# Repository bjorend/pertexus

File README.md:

# Pertexus

## Introduction
Pertexus is a board design and firmware to allow control of
Pertec-type tape interface devices.  The board is designed around
the Teensy 4.1 board (https://www.pjrc.com/store/teensy41.html)

## Hardware Design

## Firmware

The firmware is built and programmed with the Arduino 1.8.19 GUI with the
Teensyduino 1.56 add-in (https://www.pjrc.com/teensy/td_download.html).

## Usage

The firmware presents a USB "serial" device to which a user can connect.
It implements a simple command line interface.

## Regular Commands

### date - Get or set the current date and time

#### Usage

date [MMDDhhmm[[CC]YY][.ss]]

#### Examples

To set the date:

```
PERTEXUS> date 112921532022
Tue Nov 29 21:53:08 2022
```

Sets the date to November 29, 2022, 9:53PM.

### density

### echo

### fsf

### help

### nop

### read

### reset

### rewind

### sd - Commands relating to SD storage

#### Usage
```
sd init|dir|read|rm
```

The `sd` command can:
* initialize communication with an SD card.  Note: it does not "initialize"
the SD card as in "format" it; the SD card must be already formatted in FAT32
format.
* list the contents of the SD card
* perform a test read of a tape file from the SD card (to measure performance)
* remove a single file from the SD card

### stats

### unload

### write

### erase

## Development/Debugging Commands

### cmd

### dump

### gpio

### peek

### play

### poke

### tapetest

### testread

### testwrite

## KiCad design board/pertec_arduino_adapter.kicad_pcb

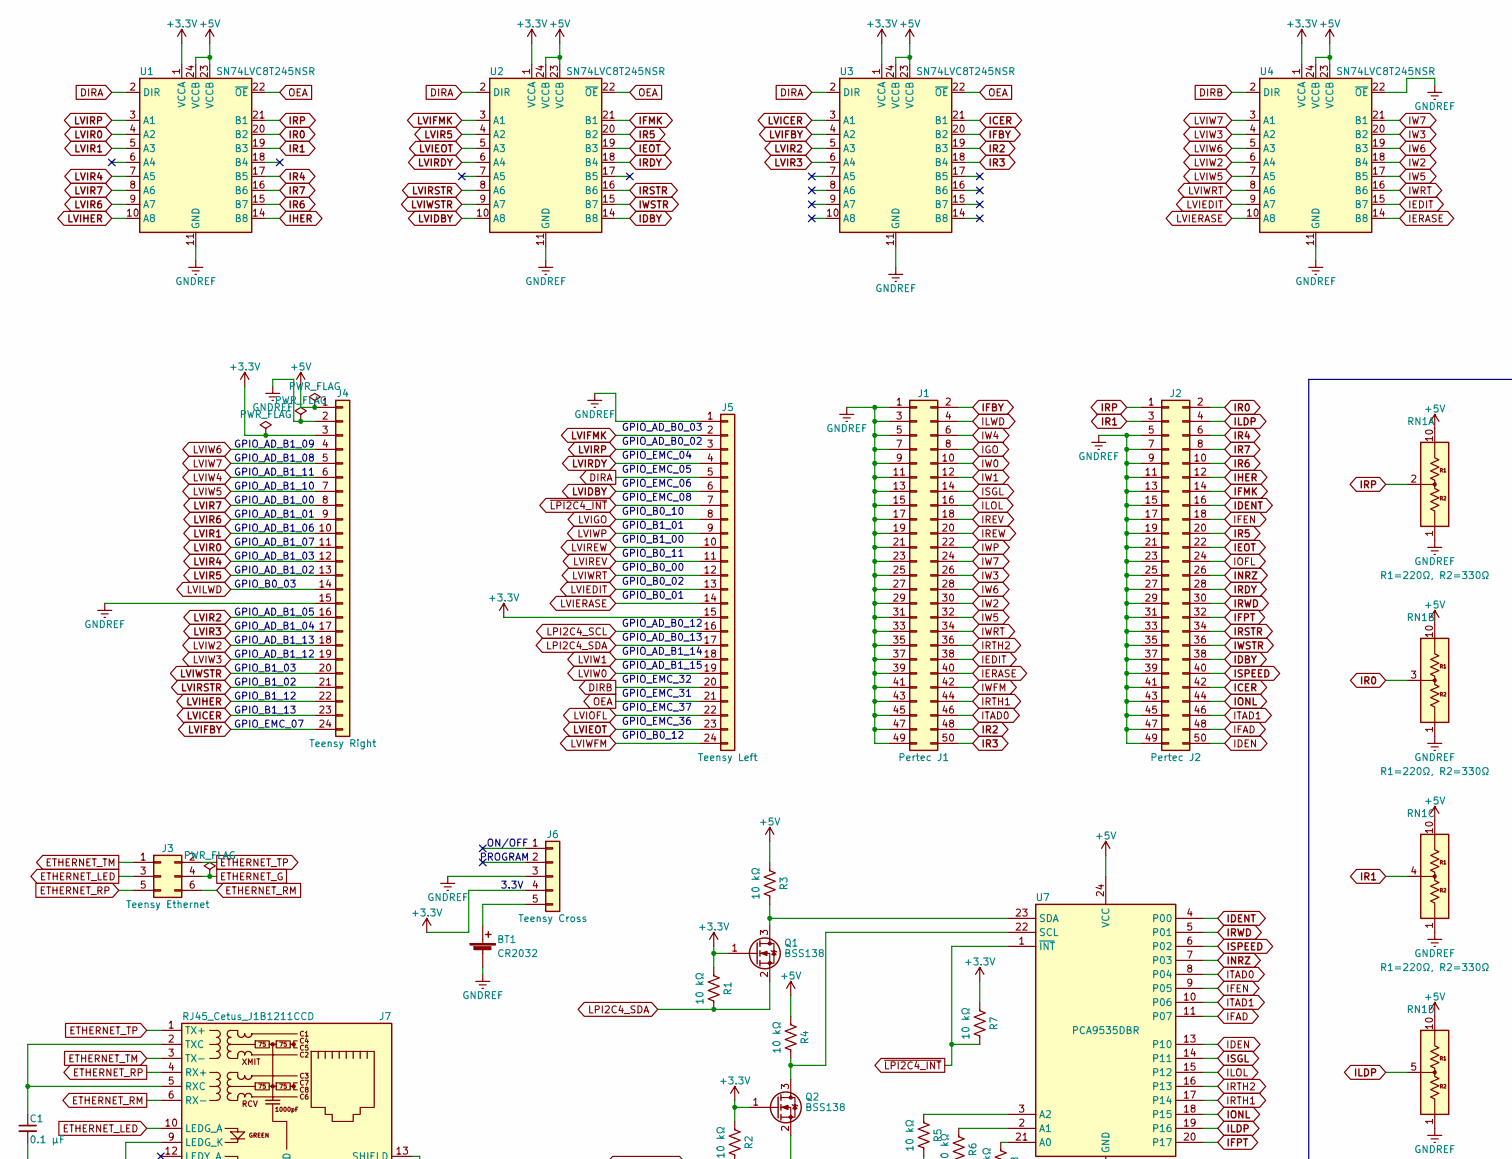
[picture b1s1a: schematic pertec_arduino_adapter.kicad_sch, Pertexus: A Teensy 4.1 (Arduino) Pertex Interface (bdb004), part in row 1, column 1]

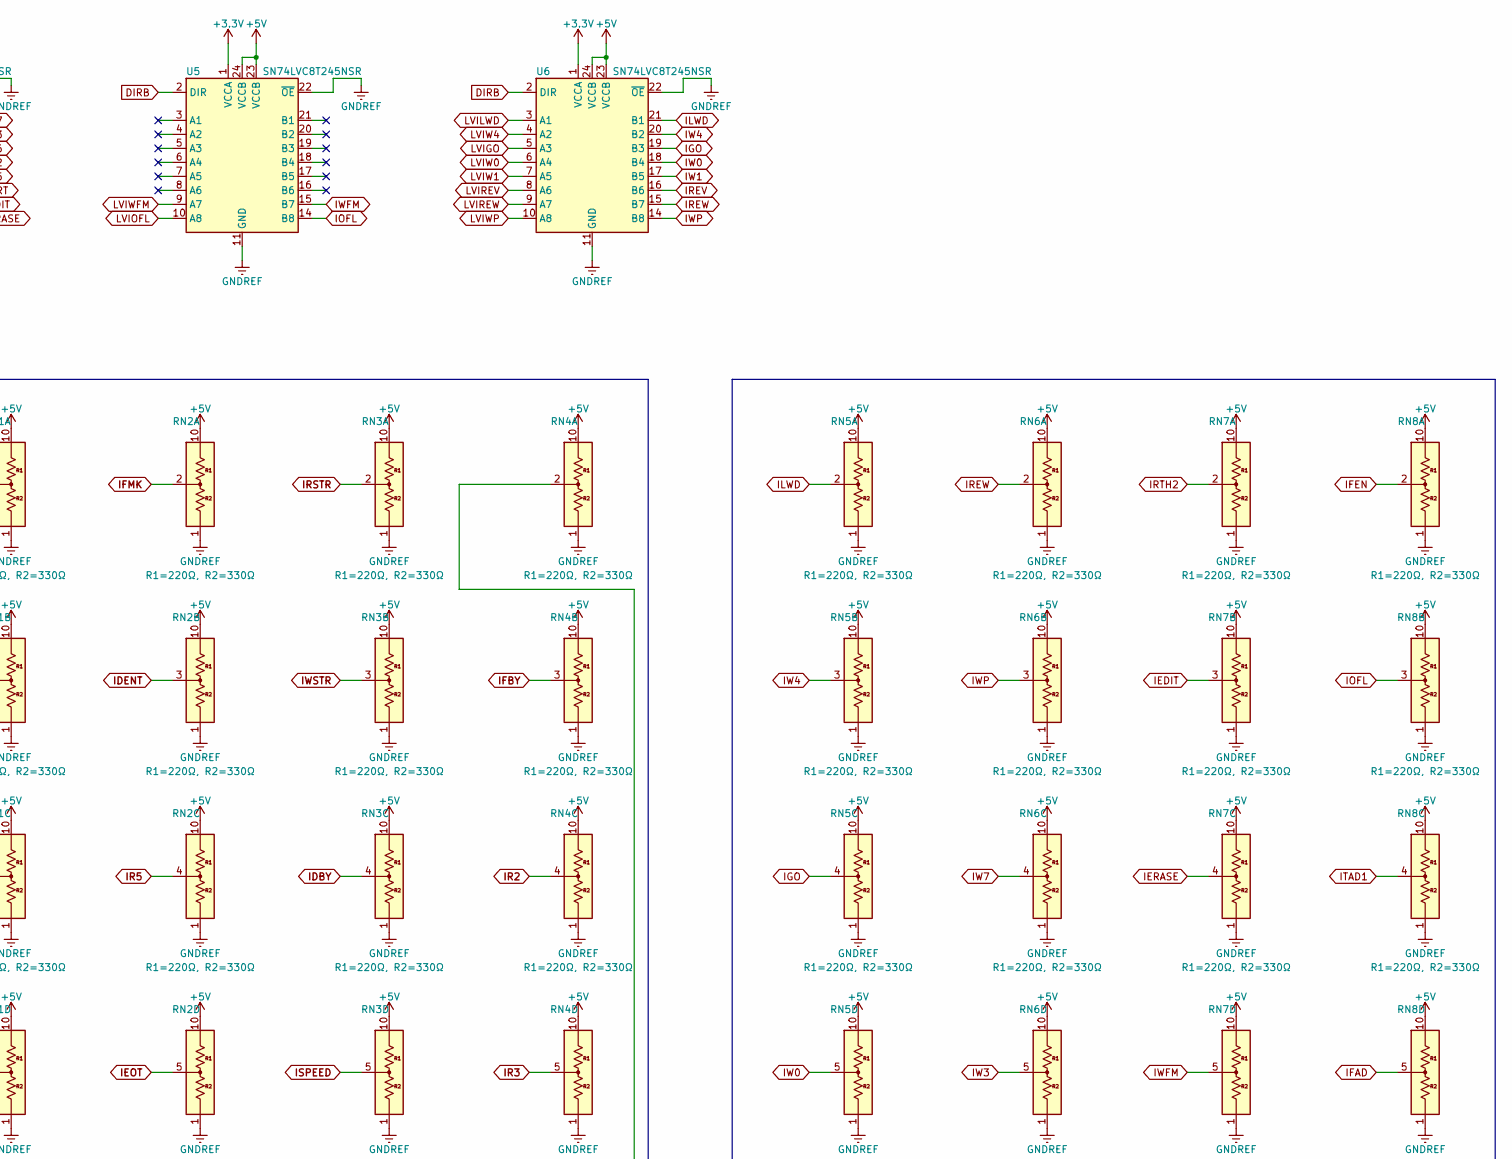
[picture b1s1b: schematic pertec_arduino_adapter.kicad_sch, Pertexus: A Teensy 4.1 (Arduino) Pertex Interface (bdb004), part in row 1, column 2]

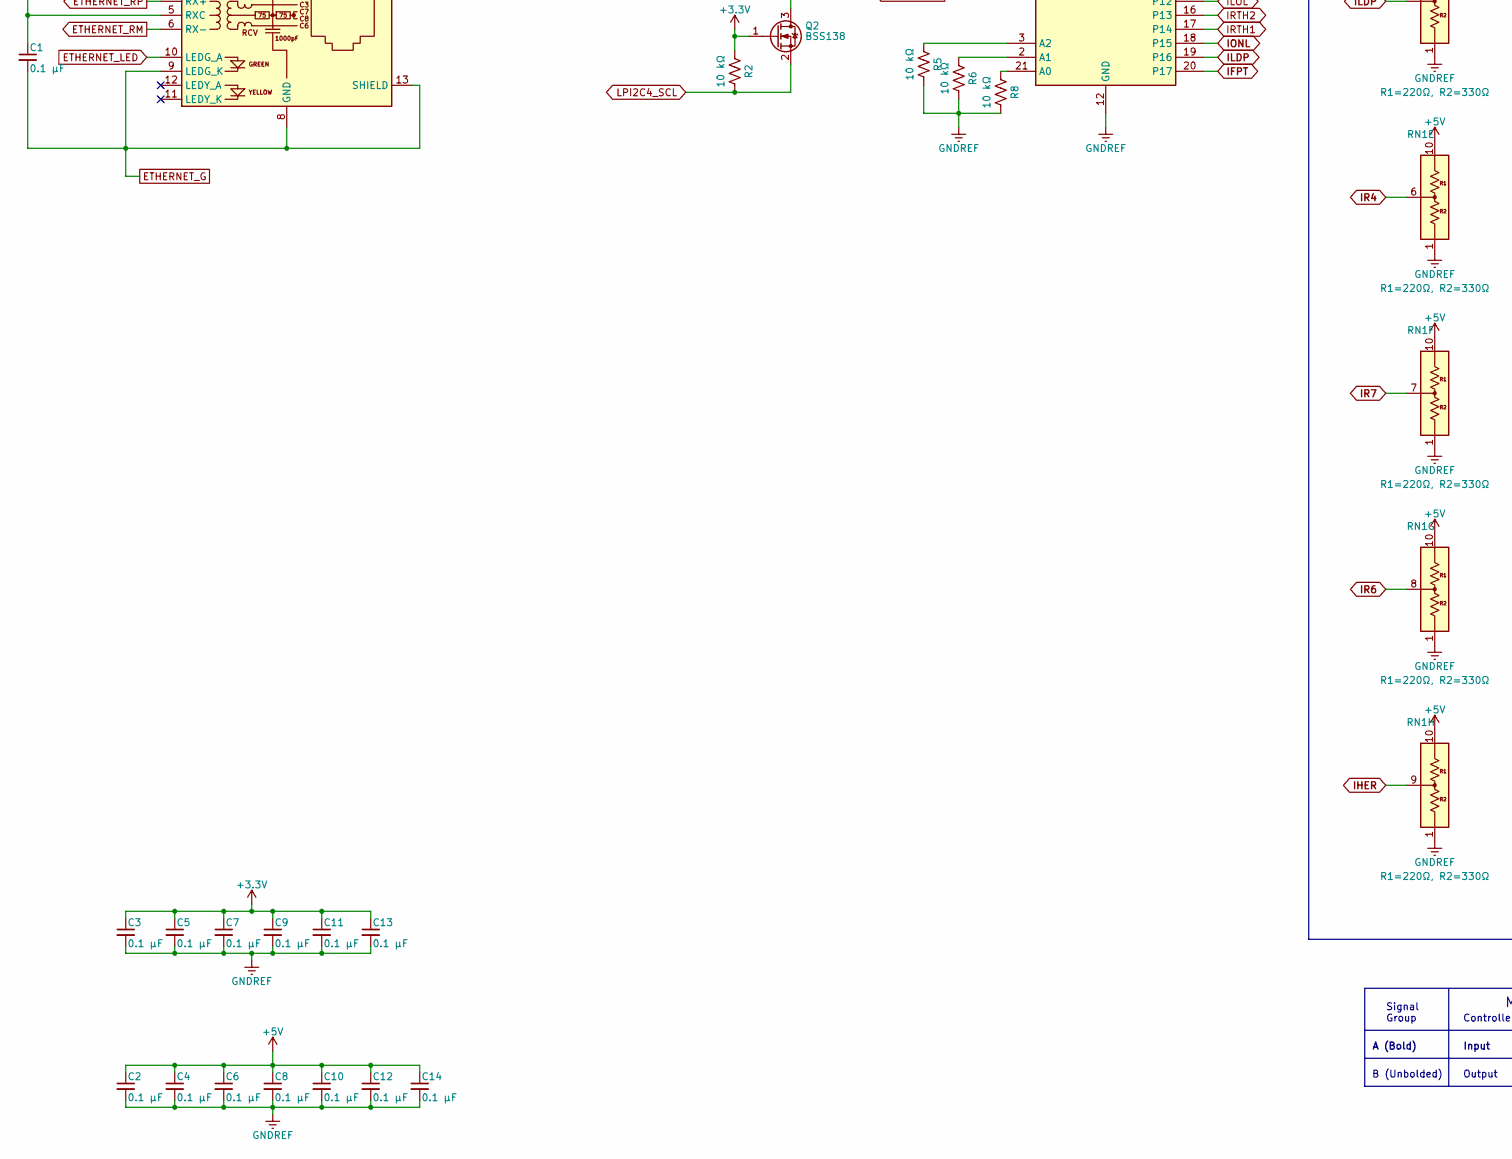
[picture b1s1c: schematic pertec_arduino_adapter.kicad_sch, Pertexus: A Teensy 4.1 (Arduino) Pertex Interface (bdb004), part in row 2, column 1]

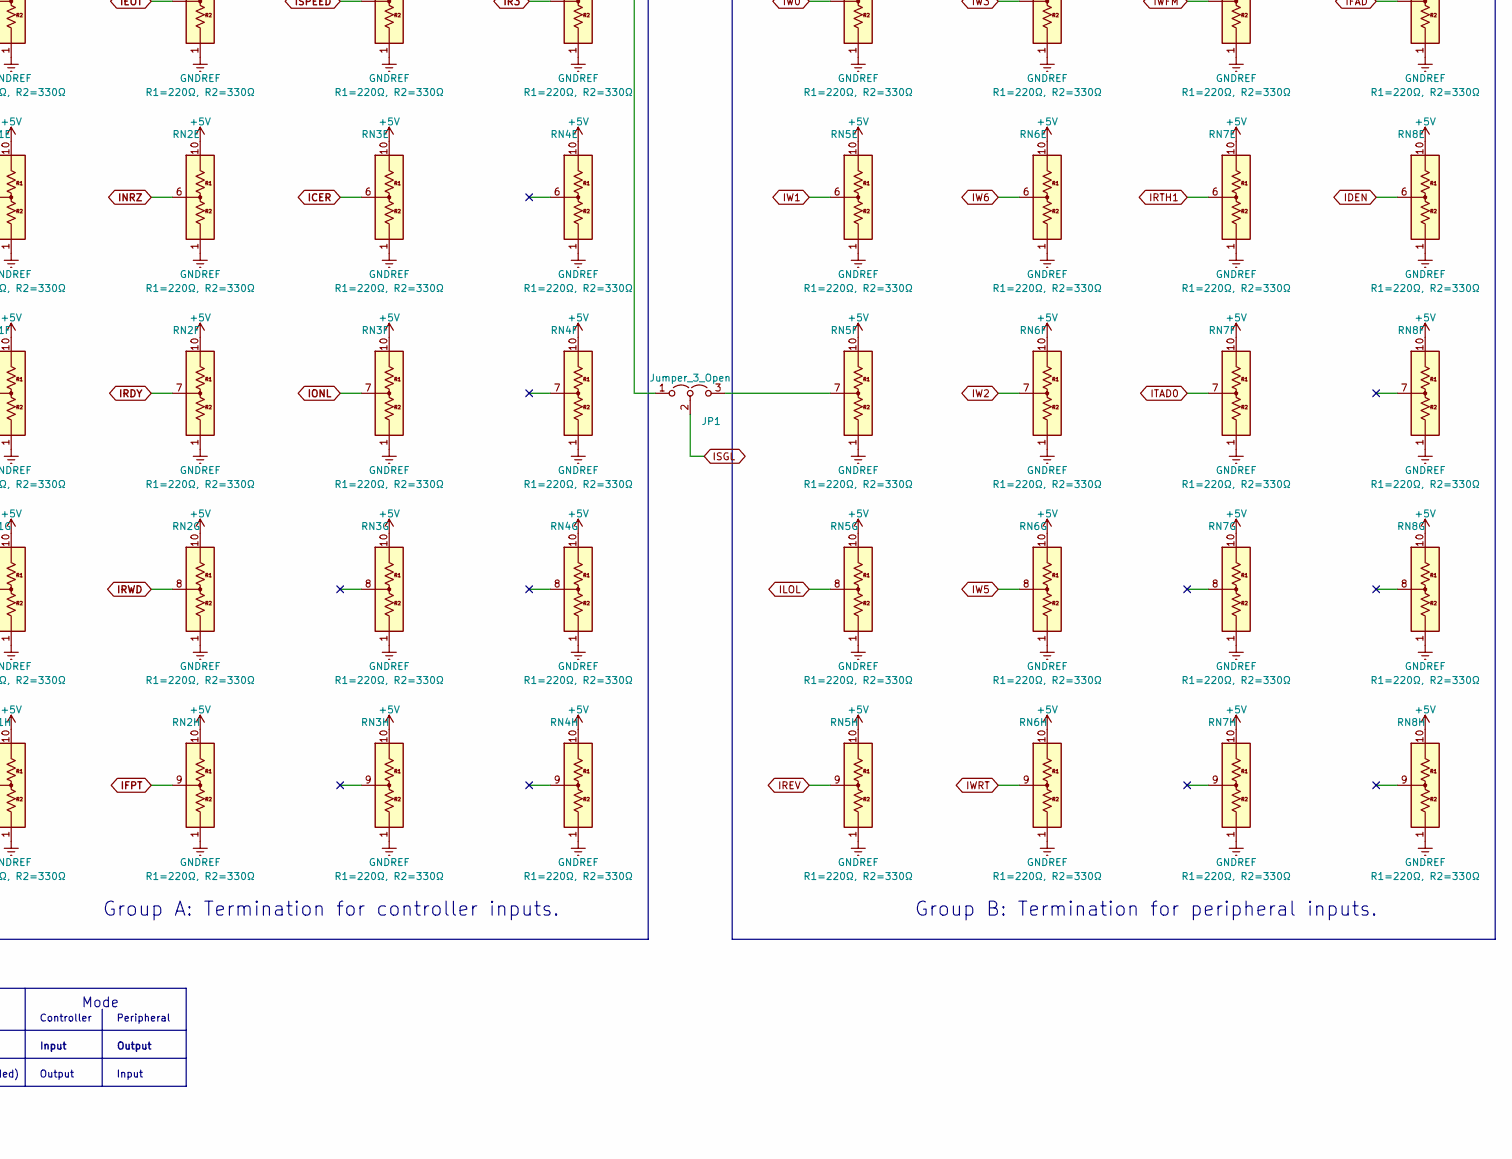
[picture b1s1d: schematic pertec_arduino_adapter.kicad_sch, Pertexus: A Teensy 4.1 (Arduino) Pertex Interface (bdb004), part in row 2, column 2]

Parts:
BT1: CR2032; BatteryHolder_Keystone_1058_1x2032
C1: 0.1 μF; C_Rect_L4.0mm_W2.5mm_P2.50mm
C2, C3, C4, C5, C6, C7, C8, C9, C10, C11, C12, C13, C14: 0.1 μF; C_0805_2012Metric_Pad1.18x1.45mm_HandSolder
J1: Pertec J1; IDC-Header_2x25_P2.54mm_Latch_Vertical
J2: Pertec J2; IDC-Header_2x25_P2.54mm_Latch_Vertical
J3: Teensy Ethernet; PinSocket_2x03_P2.00mm_Vertical_Mirror_Teensy4.1_J3
J4: Teensy Right; PinSocket_1x24_P2.54mm_Vertical_Teensy4.1_J4
J5: Teensy Left; PinSocket_1x24_P2.54mm_Vertical_Teensy4.1_J5
J6: Teensy Cross; PinSocket_1x05_P2.54mm_Vertical_Teensy4.1_J6
J7: RJ45_Cetus_J1B1211CCD; RJ45_Cetus_J1B1211CCD_Horizontal
JP1: Jumper_3_Open; PinHeader_1x03_P2.54mm_Vertical
Q1, Q2: BSS138; SOT-23
R1, R2, R3, R4, R5, R6, R7, R8: 10 kΩ; R_0805_2012Metric_Pad1.20x1.40mm_HandSolder
RN1, RN2, RN3, RN4, RN5, RN6, RN7, RN8: R1=220Ω, R2=330Ω; R_Array_SIP10
U1, U2, U3, U4, U5, U6: SN74LVC8T245NSR; SO-24_5.3x15mm_P1.27mm
U7: PCA9535DBR; SOIC-24W_7.5x15.4mm_P1.27mm

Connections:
+3V3: C3.1, C5.1, C7.1, C9.1, C11.1, C13.1, J4.3, J5.15, J6.4, Q1.1 (G), Q2.1 (G), R1.1, R2.1, R7.1, U1.1 (VCCA), U2.1 (VCCA), U3.1 (VCCA), U4.1 (VCCA), U5.1 (VCCA), U6.1 (VCCA)
+5V: C2.1, C4.1, C6.1, C8.1, C10.1, C12.1, C14.1, J4.1, R3.1, R4.1, RN1.10, RN2.10, RN3.10, RN4.10, RN5.10, RN6.10, RN7.10, RN8.10, U1.23 (VCCB), U1.24 (VCCB), U2.23 (VCCB), U2.24 (VCCB), U3.23 (VCCB), U3.24 (VCCB), U4.23 (VCCB), U4.24 (VCCB), U5.23 (VCCB), U5.24 (VCCB), U6.23 (VCCB), U6.24 (VCCB), U7.24 (VCC)
DIRA: J5.5, U1.2 (DIR), U2.2 (DIR), U3.2 (DIR)
DIRB: J5.20, U4.2 (DIR), U5.2 (DIR), U6.2 (DIR)
ETHERNET_G: C1.2, J3.4, J7.8 (GND), J7.9 (LEDG_K), J7.13 (SHIELD)
ETHERNET_LED: J3.3, J7.10 (LEDG_A)
ETHERNET_RM: J3.6, J7.6 (RX-)
ETHERNET_RP: J3.5, J7.4 (RX+)
ETHERNET_TM: J3.1, J7.3 (TX-)
ETHERNET_TP: J3.2, J7.1 (TX+)
GNDREF: BT1.2 (-), C2.2, C3.2, C4.2, C5.2, C6.2, C7.2, C8.2, C9.2, C10.2, C11.2, C12.2, C13.2, C14.2, J1.1, J1.3, J1.5, J1.7, J1.9, J1.11, J1.13, J1.15, J1.17, J1.19, J1.21, J1.23, J1.25, J1.27, J1.29, J1.31, J1.33, J1.35, J1.37, J1.39, J1.41, J1.43, J1.45, J1.47, J1.49, J2.5, J2.7, J2.9, J2.11, J2.13, J2.15, J2.17, J2.19, J2.21, J2.23, J2.25, J2.27, J2.29, J2.31, J2.33, J2.35, J2.37, J2.39, J2.41, J2.43, J2.45, J2.47, J2.49, J4.2, J4.15, J5.1, J6.3, R5.2, R6.2, R8.2, RN1.1, RN2.1, RN3.1, RN4.1, RN5.1, RN6.1, RN7.1, RN8.1, U1.11 (GND), U1.12 (GND), U1.13 (GND), U2.11 (GND), U2.12 (GND), U2.13 (GND), U3.11 (GND), U3.12 (GND), U3.13 (GND), U4.11 (GND), U4.12 (GND), U4.13 (GND), U4.22 (~OE), U5.11 (GND), U5.12 (GND), U5.13 (GND), U5.22 (~OE), U6.11 (GND), U6.12 (GND), U6.13 (GND), U6.22 (~OE), U7.12 (GND)
ICER: J2.42, RN3.6, U3.21 (B1)
IDBY: J2.38, RN3.4, U2.14 (B8)
IDEN: J2.50, RN8.6, U7.13 (P10)
IDENT: J2.16, RN2.3, U7.4 (P00)
IEDIT: J1.38, RN7.3, U4.15 (B7)
IEOT: J2.22, RN2.5, U2.19 (B3)
IERASE: J1.40, RN7.4, U4.14 (B8)
IFAD: J2.48, RN8.5, U7.11 (P07)
IFBY: J1.2, RN4.3, U3.20 (B2)
IFEN: J2.18, RN8.2, U7.9 (P05)
IFMK: J2.14, RN2.2, U2.21 (B1)
IFPT: J2.32, RN2.9, U7.20 (P17)
IGO: J1.8, RN5.4, U6.19 (B3)
IHER: J2.12, RN1.9, U1.14 (B8)
ILDP: J2.4, RN1.5, U7.19 (P16)
ILOL: J1.16, RN5.8, U7.15 (P12)
ILWD: J1.4, RN5.2, U6.21 (B1)
INRZ: J2.26, RN2.6, U7.7 (P03)
IOFL: J2.24, RN8.3, U5.14 (B8)
IONL: J2.44, RN3.7, U7.18 (P15)
IR0: J2.2, RN1.3, U1.20 (B2)
IR1: J2.3, RN1.4, U1.19 (B3)
IR2: J1.48, RN4.4, U3.19 (B3)
IR3: J1.50, RN4.5, U3.18 (B4)
IR4: J2.6, RN1.6, U1.17 (B5)
IR5: J2.20, RN2.4, U2.20 (B2)
IR6: J2.10, RN1.8, U1.15 (B7)
IR7: J2.8, RN1.7, U1.16 (B6)
IRDY: J2.28, RN2.7, U2.18 (B4)
IREV: J1.18, RN5.9, U6.16 (B6)
IREW: J1.20, RN6.2, U6.15 (B7)
IRP: J2.1, RN1.2, U1.21 (B1)
IRSTR: J2.34, RN3.2, U2.16 (B6)
IRTH1: J1.44, RN7.6, U7.17 (P14)
IRTH2: J1.36, RN7.2, U7.16 (P13)
IRWD: J2.30, RN2.8, U7.5 (P01)
ISGL: J1.14, JP1.2 (C), U7.14 (P11)
ISPEED: J2.40, RN3.5, U7.6 (P02)
ITAD0: J1.46, RN7.7, U7.8 (P04)
ITAD1: J2.46, RN8.4, U7.10 (P06)
IW0: J1.10, RN5.5, U6.18 (B4)
IW1: J1.12, RN5.6, U6.17 (B5)
IW2: J1.30, RN6.7, U4.18 (B4)
IW3: J1.26, RN6.5, U4.20 (B2)
IW4: J1.6, RN5.3, U6.20 (B2)
IW5: J1.32, RN6.8, U4.17 (B5)
IW6: J1.28, RN6.6, U4.19 (B3)
IW7: J1.24, RN6.4, U4.21 (B1)
IWFM: J1.42, RN7.5, U5.15 (B7)
IWP: J1.22, RN6.3, U6.14 (B8)
IWRT: J1.34, RN6.9, U4.16 (B6)
IWSTR: J2.36, RN3.3, U2.15 (B7)
LPI2C4_SCL: J5.16, Q2.2 (S), R2.2
LPI2C4_SDA: J5.17, Q1.2 (S), R1.2
LVICER: J4.23, U3.3 (A1)
LVIDBY: J5.6, U2.10 (A8)
LVIEDIT: J5.13, U4.9 (A7)
LVIEOT: J5.23, U2.5 (A3)
LVIERASE: J5.14, U4.10 (A8)
LVIFBY: J4.24, U3.4 (A2)
LVIFMK: J5.2, U2.3 (A1)
LVIGO: J5.8, U6.5 (A3)
LVIHER: J4.22, U1.10 (A8)
LVILWD: J4.14, U6.3 (A1)
LVIOFL: J5.22, U5.10 (A8)
LVIR0: J4.11, U1.4 (A2)
LVIR1: J4.10, U1.5 (A3)
LVIR2: J4.16, U3.5 (A3)
LVIR3: J4.17, U3.6 (A4)
LVIR4: J4.12, U1.7 (A5)
LVIR5: J4.13, U2.4 (A2)
LVIR6: J4.9, U1.9 (A7)
LVIR7: J4.8, U1.8 (A6)
LVIRDY: J5.4, U2.6 (A4)
LVIREV: J5.11, U6.8 (A6)
LVIREW: J5.10, U6.9 (A7)
LVIRP: J5.3, U1.3 (A1)
LVIRSTR: J4.21, U2.8 (A6)
LVIW0: J5.19, U6.6 (A4)
LVIW1: J5.18, U6.7 (A5)
LVIW2: J4.18, U4.6 (A4)
LVIW3: J4.19, U4.4 (A2)
LVIW4: J4.6, U6.4 (A2)
LVIW5: J4.7, U4.7 (A5)
LVIW6: J4.4, U4.5 (A3)
LVIW7: J4.5, U4.3 (A1)
LVIWFM: J5.24, U5.9 (A7)
LVIWP: J5.9, U6.10 (A8)
LVIWRT: J5.12, U4.8 (A6)
LVIWSTR: J4.20, U2.9 (A7)
unnamed: BT1.1 (+), J6.5
unnamed: C1.1, J7.2 (TXC), J7.5 (RXC)
unnamed: JP1.1 (A), RN4.2
unnamed: JP1.3 (B), RN5.7
unnamed: Q1.3 (D), R3.2, U7.23 (SDA)
unnamed: Q2.3 (D), R4.2, U7.22 (SCL)
unnamed: R5.1, U7.3 (A2)
unnamed: R6.1, U7.2 (A1)
unnamed: R8.1, U7.21 (A0)
OEA: J5.21, U1.22 (~OE), U2.22 (~OE), U3.22 (~OE)
~LPI2C4_INT: J5.7, R7.2, U7.1 (~INT)

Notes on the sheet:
A (Bold)
GPIO_EMC_32
Controller
GPIO_B1_00
3.3V
GPIO_AD_B0_02
GPIO_B0_02
GPIO_AD_B1_13
GPIO_AD_B1_07
GPIO_AD_B0_13
GPIO_EMC_07
Input
GPIO_B1_12
Signal Group
GPIO_B0_11
Mode
GPIO_EMC_04
GPIO_AD_B1_10
Output
GPIO_AD_B1_03
PROGRAM
GPIO_AD_B0_12
Group B: Termination for peripheral inputs.
GPIO_B0_01
GPIO_B0_12
ON/OFF
Peripheral
GPIO_B0_00
GPIO_B1_03
GPIO_EMC_36
GPIO_AD_B1_15
GPIO_AD_B1_02
B (Unbolded)
GPIO_AD_B1_01
Group A: Termination for controller inputs.
GPIO_EMC_05
GPIO_EMC_06
GPIO_EMC_37
GPIO_AD_B0_03
GPIO_AD_B1_06

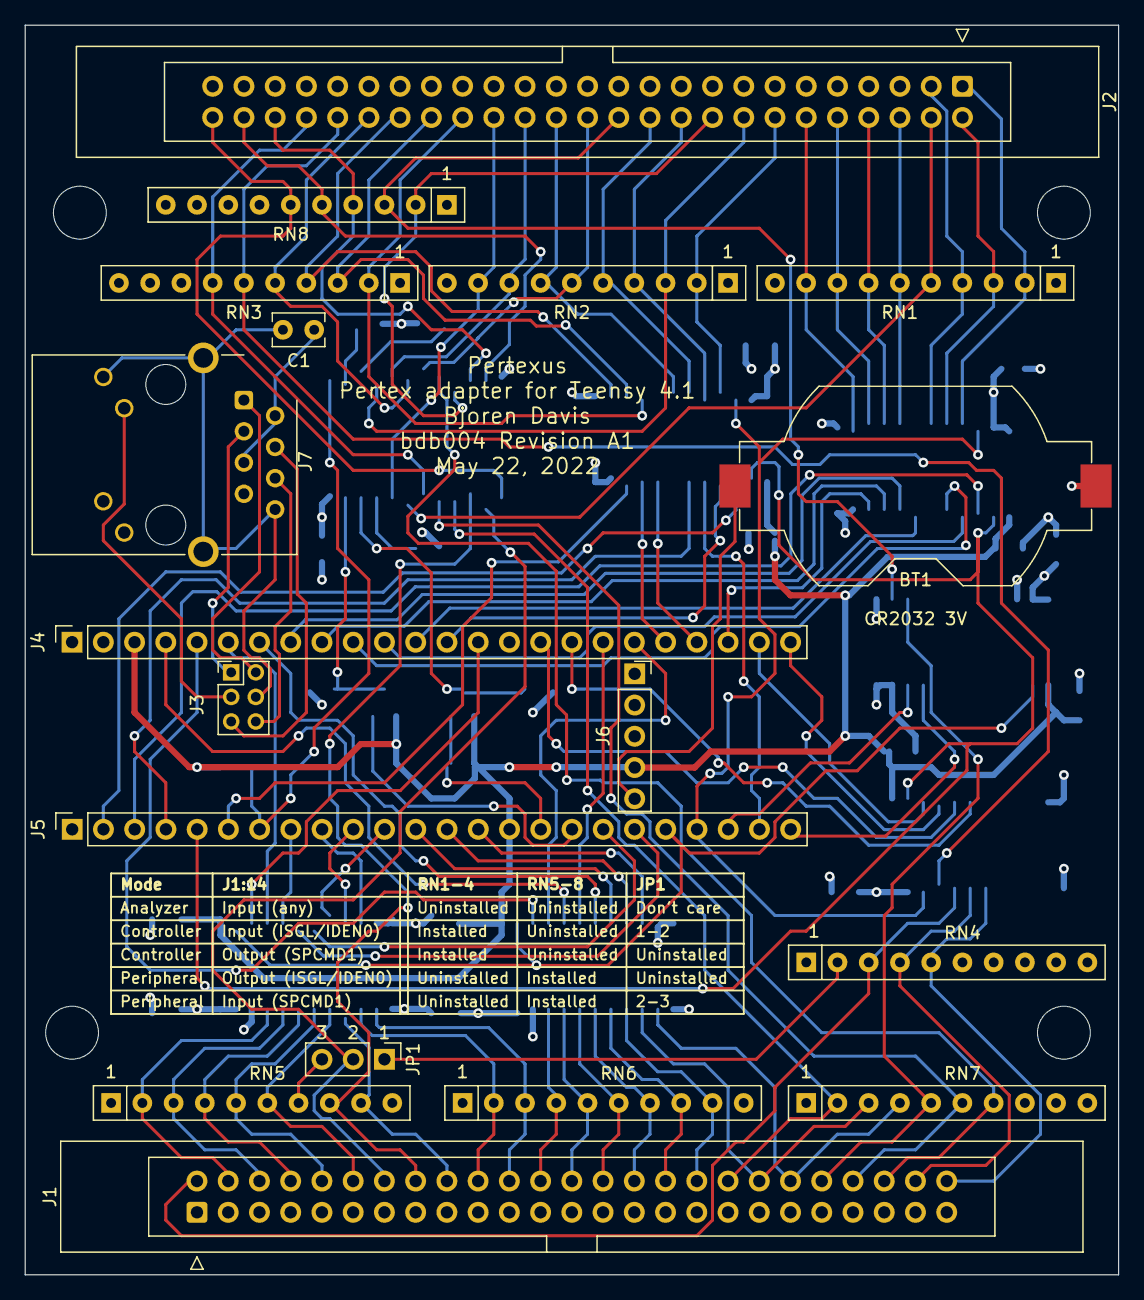
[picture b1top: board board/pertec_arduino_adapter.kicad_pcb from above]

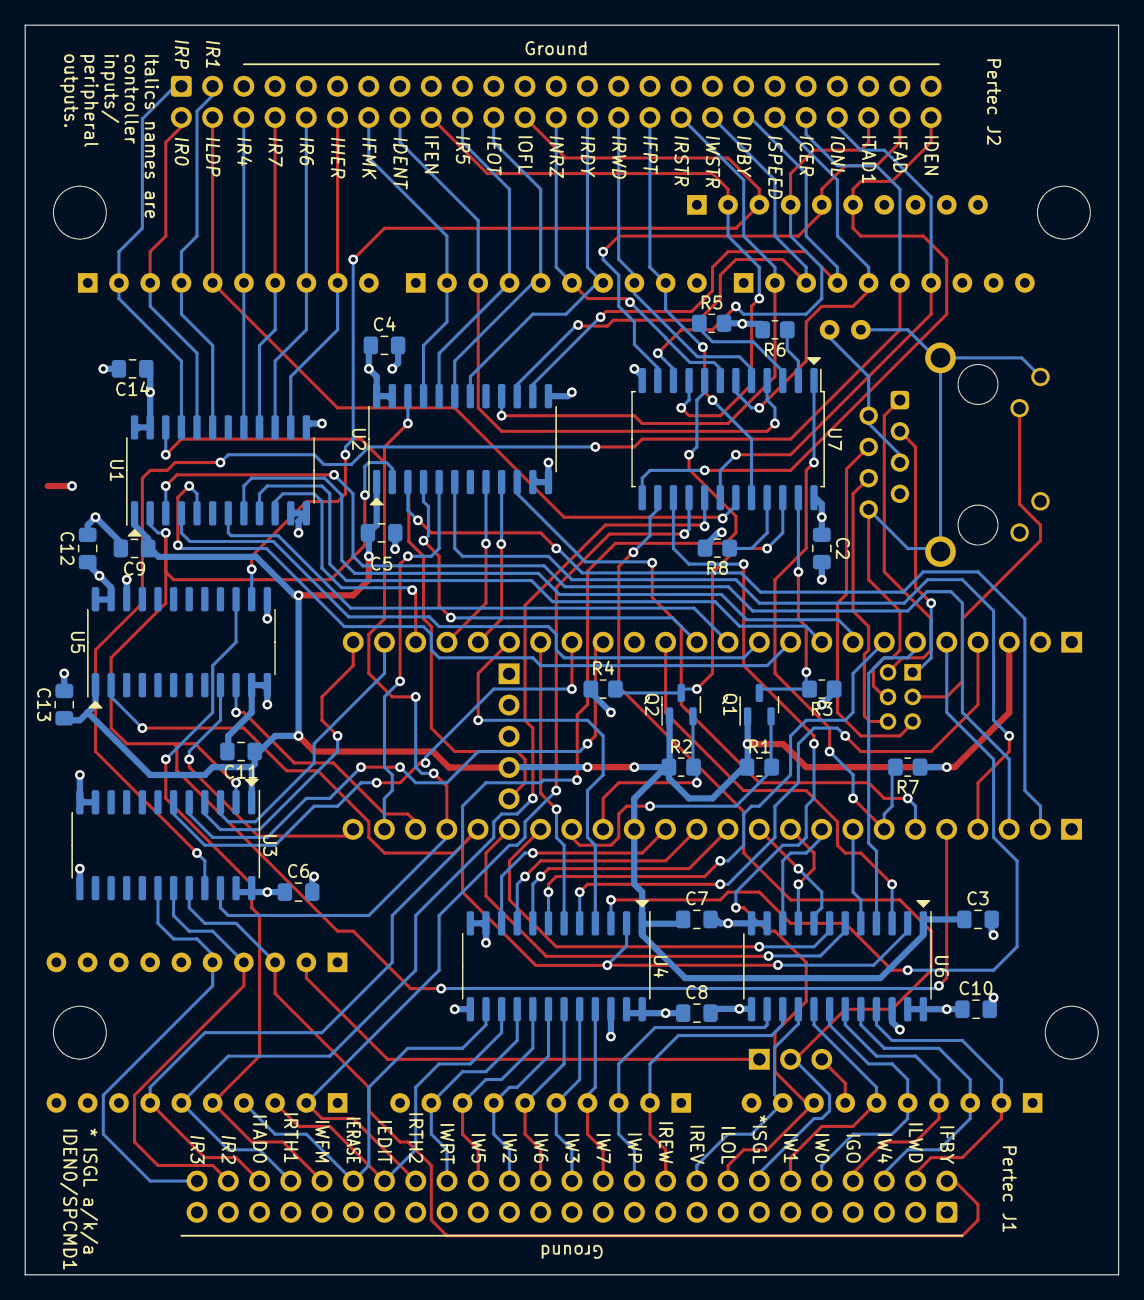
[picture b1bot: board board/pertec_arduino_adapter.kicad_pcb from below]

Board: 4 copper layers, 88.9 x 101.6 mm, 48 parts (30 on the bottom side), 112 nets.

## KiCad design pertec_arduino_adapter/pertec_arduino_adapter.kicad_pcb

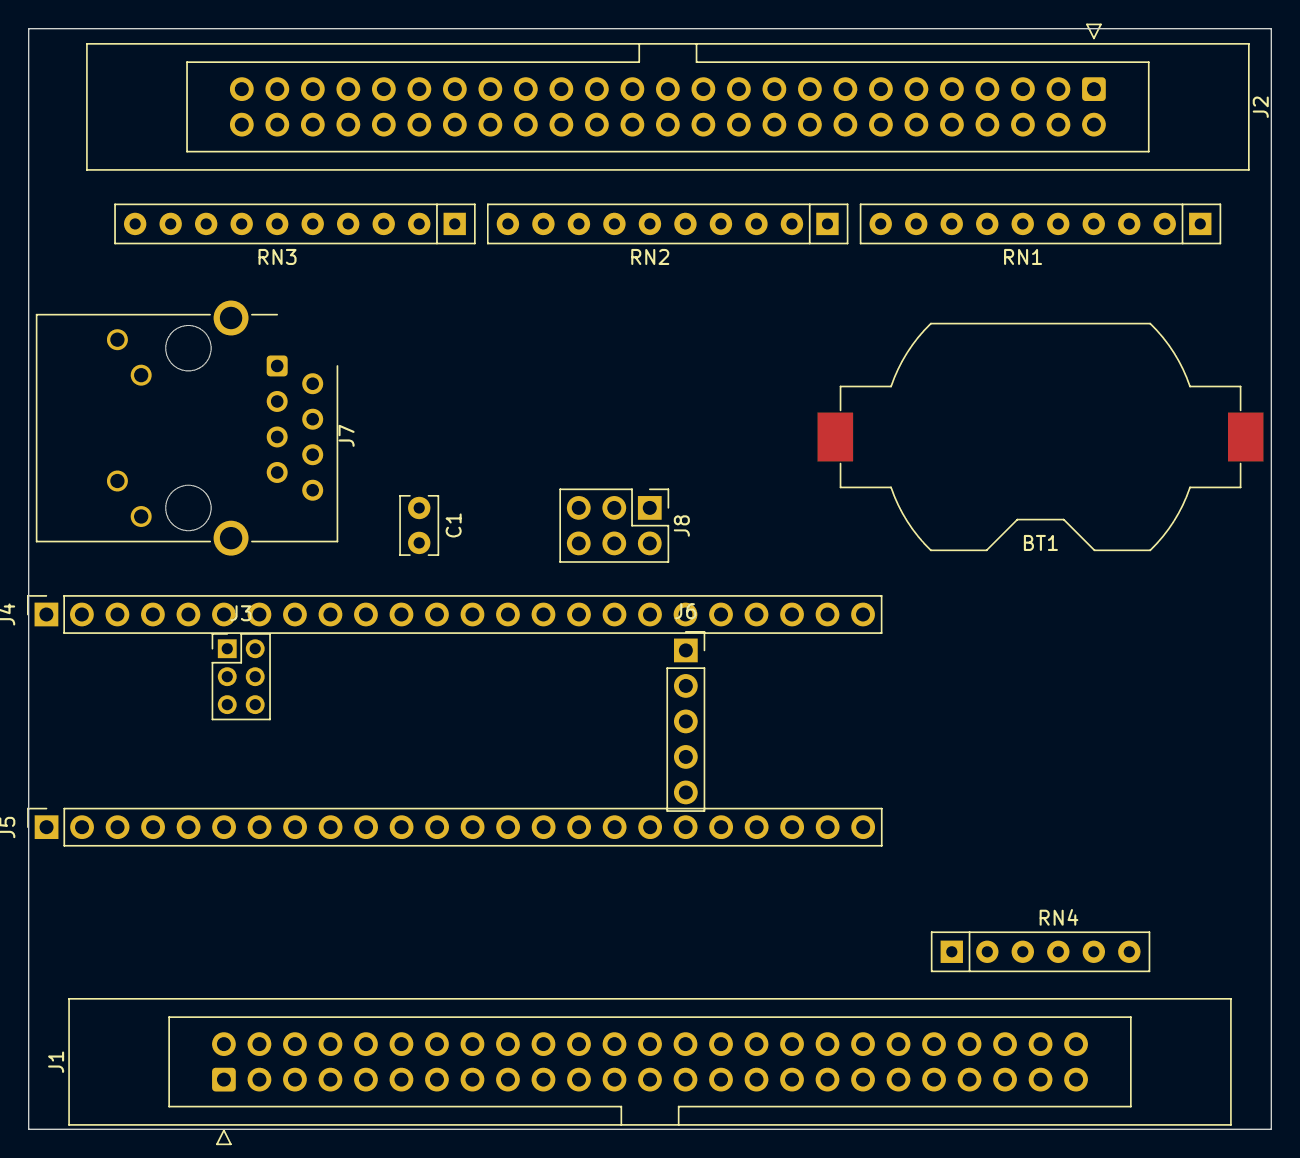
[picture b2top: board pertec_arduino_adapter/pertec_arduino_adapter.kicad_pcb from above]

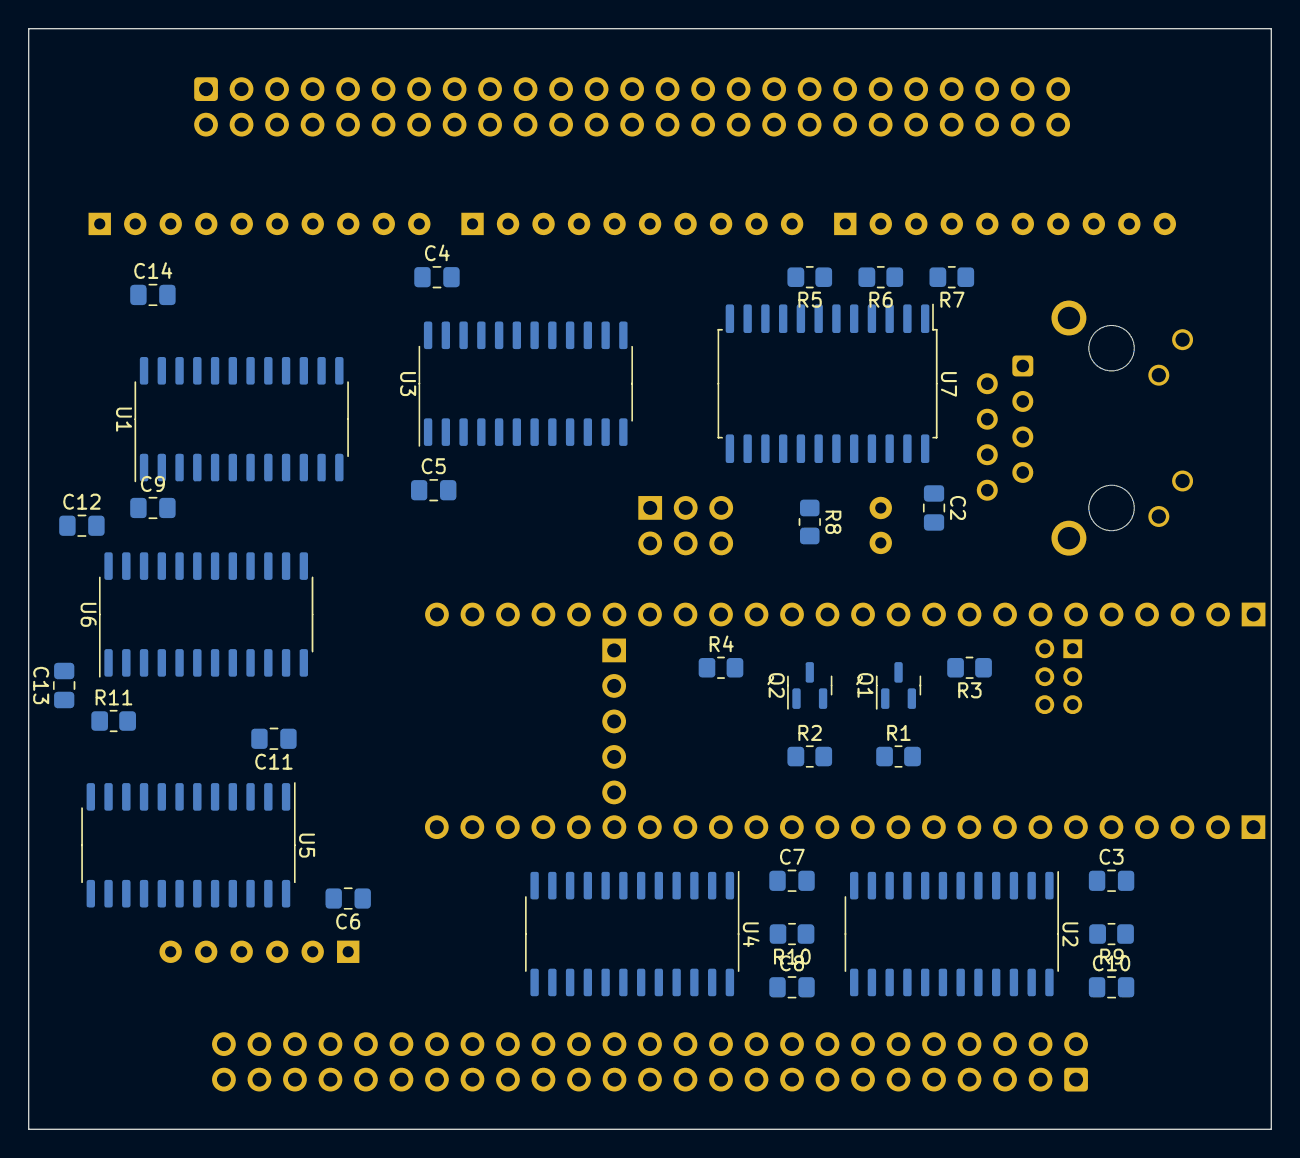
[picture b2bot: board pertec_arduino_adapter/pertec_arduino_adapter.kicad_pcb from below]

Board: 2 copper layers, 88.9 x 78.7 mm, 47 parts (33 on the bottom side), 115 nets, no tracks yet.

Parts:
BT1: CR2032; BatteryHolder_Keystone_1058_1x2032
C1: 0.1 μF; C_Rect_L4.0mm_W2.5mm_P2.50mm
C2, C3, C4, C5, C6, C7, C8, C9, C10, C11, C12, C13, C14: 0.1 μF; C_0805_2012Metric_Pad1.18x1.45mm_HandSolder
J1, J2: Conn_02x25_Odd_Even; IDC-Header_2x25_P2.54mm_Latch_Vertical
J3: Conn_02x03_Odd_Even; PinSocket_2x03_P2.00mm_Vertical_Mirror
J4, J5: Conn_01x24; PinSocket_1x24_P2.54mm_Vertical
J6: Conn_01x05; PinSocket_1x05_P2.54mm_Vertical
J7: RJ45_Cetus_J1B1211CCD; RJ45_Cetus_J1B1211CCD_Horizontal
J8: Conn_02x03_Odd_Even; PinHeader_2x03_P2.54mm_Vertical
Q1, Q2: BSS138; SOT-23
R1, R2, R3, R4, R5, R6, R7, R8, R9, R10, R11: 10 kΩ; R_0805_2012Metric_Pad1.20x1.40mm_HandSolder
RN1, RN2, RN3: R1=220Ω, R2=330Ω; R_Array_SIP10
RN4: R1=220Ω, R2=330Ω; R_Array_SIP6
U1, U2, U3, U4, U5, U6: SN74LVC8T245NSR; SO-24_5.3x15mm_P1.27mm
U7: PCA9535DBR; SOIC-24W_7.5x15.4mm_P1.27mm

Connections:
+3V3: C3.1, C5.1, C7.1, C9.1, C11.1, C13.1, J4.3, J5.15, Q1.1 (G), Q2.1 (G), R1.1, R2.1, R7.1, R9.1, R10.1, R11.1, U1.1 (VCCA), U2.1 (VCCA), U3.1 (VCCA), U4.1 (VCCA), U5.1 (VCCA), U6.1 (VCCA)
+5V: C2.1, C4.1, C6.1, C8.1, C10.1, C12.1, C14.1, J4.1, R3.1, R4.1, RN1.10, RN2.10, RN3.10, RN4.6, U1.23 (VCCB), U1.24 (VCCB), U2.23 (VCCB), U2.24 (VCCB), U3.23 (VCCB), U3.24 (VCCB), U4.23 (VCCB), U4.24 (VCCB), U5.23 (VCCB), U5.24 (VCCB), U6.23 (VCCB), U6.24 (VCCB), U7.24 (VCC)
ETHERNET_G: C1.2, J3.4, J7.8 (GND), J7.9 (LEDG_K), J7.13 (SHIELD)
ETHERNET_LED: J3.3, J7.10 (LEDG_A)
ETHERNET_RM: J3.6, J7.6 (RX-)
ETHERNET_RP: J3.5, J7.4 (RX+)
ETHERNET_TM: J3.1, J7.3 (TX-)
ETHERNET_TP: J3.2, J7.1 (TX+)
GNDREF: BT1.2 (-), C2.2, C3.2, C4.2, C5.2, C6.2, C7.2, C8.2, C9.2, C10.2, C11.2, C12.2, C13.2, C14.2, J1.1, J1.3, J1.5, J1.7, J1.9, J1.11, J1.13, J1.15, J1.17, J1.19, J1.21, J1.23, J1.25, J1.27, J1.29, J1.31, J1.33, J1.35, J1.37, J1.39, J1.41, J1.43, J1.45, J1.47, J1.49, J2.5, J2.7, J2.9, J2.11, J2.13, J2.15, J2.17, J2.19, J2.21, J2.23, J2.25, J2.27, J2.29, J2.31, J2.33, J2.35, J2.37, J2.39, J2.41, J2.43, J2.45, J2.47, J2.49, J4.2, J4.15, J5.1, J6.3, J8.1, J8.3, J8.5, R5.2, R6.2, R8.2, RN1.1, RN2.1, RN3.1, RN4.1, U1.2 (DIR), U1.11 (GND), U1.12 (GND), U1.13 (GND), U1.22 (~OE), U2.11 (GND), U2.12 (GND), U2.13 (GND), U2.22 (~OE), U3.2 (DIR), U3.11 (GND), U3.12 (GND), U3.13 (GND), U3.22 (~OE), U4.11 (GND), U4.12 (GND), U4.13 (GND), U4.22 (~OE), U5.2 (DIR), U5.11 (GND), U5.12 (GND), U5.13 (GND), U5.22 (~OE), U6.11 (GND)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
GPIO_AD_B0_02: J5.3, U1.3 (A1)
GPIO_AD_B0_03: J5.2, U3.3 (A1)
GPIO_AD_B0_12: J5.16, Q2.2 (S), R2.2
GPIO_AD_B0_13: J5.17, Q1.2 (S), R1.2
GPIO_AD_B1_00: J4.8, U1.8 (A6)
GPIO_AD_B1_01: J4.9, U1.9 (A7)
GPIO_AD_B1_02: J4.13, U3.4 (A2)
GPIO_AD_B1_03: J4.12, U1.7 (A5)
GPIO_AD_B1_04: J4.17, U5.6 (A4)
GPIO_AD_B1_05: J4.16, U5.5 (A3)
GPIO_AD_B1_06: J4.10, U1.5 (A3)
GPIO_AD_B1_07: J4.11, U1.4 (A2)
GPIO_AD_B1_08: J4.5, U4.3 (A1)
GPIO_AD_B1_09: J4.4, U4.5 (A3)
GPIO_AD_B1_10: J4.7, U4.7 (A5)
GPIO_AD_B1_11: J4.6, U2.4 (A2)
GPIO_AD_B1_12: J4.19, U4.4 (A2)
GPIO_AD_B1_13: J4.18, U4.6 (A4)
GPIO_AD_B1_14: J5.18, U2.7 (A5)
GPIO_AD_B1_15: J5.19, U2.6 (A4)
GPIO_B0_00: J5.12, U4.8 (A6)
GPIO_B0_01: J5.14, U4.10 (A8)
GPIO_B0_02: J5.13, U4.9 (A7)
GPIO_B0_03: J4.14, U2.3 (A1)
GPIO_B0_10: J5.8, U2.5 (A3)
GPIO_B0_11: J5.11, U2.8 (A6)
GPIO_B0_12: J5.24, U6.9 (A7)
GPIO_B1_00: J5.10, U2.9 (A7)
GPIO_B1_01: J5.9, U2.10 (A8)
GPIO_B1_02: J4.21, U3.8 (A6)
GPIO_B1_03: J4.20, U3.9 (A7)
GPIO_B1_12: J4.22, U1.10 (A8)
GPIO_B1_13: J4.23, U5.3 (A1)
GPIO_EMC_04: J5.4, U3.6 (A4)
GPIO_EMC_05: J5.5, U3.7 (A5)
GPIO_EMC_06: J5.6, U3.10 (A8)
GPIO_EMC_07: J4.24, U5.4 (A2)
GPIO_EMC_08: J5.7, R7.2, U7.1 (~INT)
GPIO_EMC_31: J5.21, J8.6
GPIO_EMC_32: J5.20, U1.6 (A4)
GPIO_EMC_36: J5.23, U3.5 (A3)
GPIO_EMC_37: J5.22, U6.10 (A8)
ICER: J2.42, RN3.6, U5.21 (B1)
IDBY: J2.38, RN3.4, U3.14 (B8)
IDEN: J2.50, U7.13 (P10)
IDENT: J2.16, RN2.3, U7.4 (P00)
IEDIT: J1.38, U4.15 (B7)
IEOT: J2.22, RN2.5, U3.19 (B3)
IERASE: J1.40, U4.14 (B8)
IFAD: J2.48, U7.11 (P07)
IFBY: J1.2, RN4.2, U5.20 (B2)
IFEN: J2.18, U7.9 (P05)
IFMK: J2.14, RN2.2, U3.21 (B1)
IFPT: J2.32, RN2.9, U3.17 (B5)
IGO: J1.8, U2.19 (B3)
IHER: J2.12, RN1.9, U1.14 (B8)
ILDP: J2.4, RN1.5, U1.18 (B4)
ILOL: J1.16, U7.15 (P12)
ILWD: J1.4, U2.21 (B1)
INRZ: J2.26, RN2.6, U7.7 (P03)
IOFL: J2.24, U6.14 (B8)
IONL: J2.44, RN3.7, U7.18 (P15)
IR0: J2.2, RN1.3, U1.20 (B2)
IR1: J2.3, RN1.4, U1.19 (B3)
IR2: J1.48, RN4.3, U5.19 (B3)
IR3: J1.50, RN4.4, U5.18 (B4)
IR4: J2.6, RN1.6, U1.17 (B5)
IR5: J2.20, RN2.4, U3.20 (B2)
IR6: J2.10, RN1.8, U1.15 (B7)
IR7: J2.8, RN1.7, U1.16 (B6)
IRDY: J2.28, RN2.7, U3.18 (B4)
IREV: J1.18, U2.16 (B6)
IREW: J1.20, U2.15 (B7)
IRP: J2.1, RN1.2, U1.21 (B1)
IRSTR: J2.34, RN3.2, U3.16 (B6)
IRTH1: J1.44, U7.17 (P14)
IRTH2: J1.36, U7.16 (P13)
IRWD: J2.30, RN2.8, U7.5 (P01)
ISGL: J1.14, U7.14 (P11)
ISPEED: J2.40, RN3.5, U7.6 (P02)
ITAD0: J1.46, U7.8 (P04)
ITAD1: J2.46, U7.10 (P06)
IW0: J1.10, U2.18 (B4)
IW1: J1.12, U2.17 (B5)
IW2: J1.30, U4.18 (B4)
IW3: J1.26, U4.20 (B2)
IW4: J1.6, U2.20 (B2)
IW5: J1.32, U4.17 (B5)
IW6: J1.28, U4.19 (B3)
IW7: J1.24, U4.21 (B1)
IWFM: J1.42, U6.15 (B7)
IWP: J1.22, U2.14 (B8)
IWRT: J1.34, U4.16 (B6)
IWSTR: J2.36, RN3.3, U3.15 (B7)
unnamed: BT1.1 (+), J6.5
unnamed: C1.1, J7.2 (TXC), J7.5 (RXC)
unnamed: Q1.3 (D), R3.2, U7.23 (SDA)
unnamed: Q2.3 (D), R4.2, U7.22 (SCL)
unnamed: R5.1, U7.3 (A2)
unnamed: R6.1, U7.2 (A1)
unnamed: R8.1, U7.21 (A0)
unnamed: R9.2, U2.2 (DIR)
unnamed: R10.2, U4.2 (DIR)
unnamed: R11.2, U6.2 (DIR)
SPARE0: J8.2, U7.19 (P16)
SPARE1: J8.4, U7.20 (P17)

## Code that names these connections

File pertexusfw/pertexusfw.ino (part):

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#define INTCFG_IWSTR    0x00000008
#define INTCFG_IRSTR    0x00000010
#define INTCFG_IEOT     0x00000020
/* #define INTCFG_PORTEXP  0x00000040 */      /* LPI2C4_INT port expander int */
#define INTCFG_IDBY     0x00000080

/* Internal readonly data mapping these interrupts to GPIO set
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static CONSTSTRDEF(_cmd_poke_brief, "poke a byte");

static CONSTSTRDEF(_cmd_cmd_name, "cmd");
static CONSTSTRDEF(_cmd_cmd_brief, "do an aribtrary IGO command");

static CONSTSTRDEF(_cmd_density_name, "density");
static CONSTSTRDEF(_cmd_density_brief, "select the drive's density");
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    GPINFO_ENTRY("IW2",      "Write data bit 2 (LSB)", GP_IW2),
    GPINFO_ENTRY("IW1",      "Write data bit 1 (LSB)", GP_IW1),
    GPINFO_ENTRY("IW0",      "Write data bit 0 (LSB)", GP_IW0),
    GPINFO_ENTRY("IGO",      "Go pulse (command strobe)", GP_IGO),
    GPINFO_ENTRY("IWRT",     "Write", GP_IWRT),
    GPINFO_ENTRY("IERASE",   "Erase", GP_IERASE),
    GPINFO_ENTRY("IWFM",     "Write filemark", GP_IWFM),
    GPINFO_ENTRY("IEDIT",    "Edit", GP_IEDIT),
    GPINFO_ENTRY("IREV",     "Reverse", GP_IREV),
    GPINFO_ENTRY("ILWD",     "Last word; terminates write", GP_ILWD),
    GPINFO_ENTRY("ISGL",     "*Selected drive fault", GP_ISGL),
    GPINFO_ENTRY("ILOL",     "*Load on line", GP_ILOL),
    GPINFO_ENTRY("IREW",     "Rewind", GP_IREW),
    GPINFO_ENTRY("IWP",      "Write data parity", GP_IWP),
    GPINFO_ENTRY("IRTH2",    "*Write density select 2", GP_IRTH2),
    GPINFO_ENTRY("IRTH1",    "*Write density select 1", GP_IRTH1),
    GPINFO_ENTRY("ICER",     "Correctable error", GP_ICER),
    GPINFO_ENTRY("IHER",     "Hard error", GP_IHER),
    GPINFO_ENTRY("IWSTR",    "Write strobe", GP_IWSTR),
    GPINFO_ENTRY("IRSTR",    "Read strobe", GP_IRSTR),
    GPINFO_ENTRY("IDENT",    "Identifiation burst", GP_IDENT),
    GPINFO_ENTRY("IFMK",     "Filemark", GP_IFMK),
    GPINFO_ENTRY("IR7",      "Read data bit 7 (LSB)", GP_IR7),
    GPINFO_ENTRY("IR6",      "Read data bit 6", GP_IR6),
    GPINFO_ENTRY("IR5",      "Read data bit 5", GP_IR5),
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    GPINFO_ENTRY("IR2",      "Read data bit 2", GP_IR2),
    GPINFO_ENTRY("IR1",      "Read data bit 1", GP_IR1),
    GPINFO_ENTRY("IR0",      "Read data bit 0 (MSB)", GP_IR0),
    GPINFO_ENTRY("IFBY",     "Formatter busy", GP_IFBY),
    GPINFO_ENTRY("IRP",      "Read data parity", GP_IRP),
    GPINFO_ENTRY("ILDP",     "Load point", GP_ILDP),
    GPINFO_ENTRY("IEOT",     "End of tape", GP_IEOT),
    GPINFO_ENTRY("INRZ",     "3200 BPI selected", GP_INRZ),
    GPINFO_ENTRY("IRDY",     "Ready", GP_IRDY),
    GPINFO_ENTRY("IRWD",     "Rewinding", GP_IRWD),
    GPINFO_ENTRY("IFPT",     "File protected", GP_IFPT),
    GPINFO_ENTRY("IDBY",     "Data busy", GP_IDBY),
    GPINFO_ENTRY("ISPEED",   "Early EOT indicator", GP_ISPEED),
    GPINFO_ENTRY("IONL",     "Online", GP_IONL),
    GPINFO_ENTRY("ITAD0",    "Transport address 0 (MSB)", GP_ITAD0),
    GPINFO_ENTRY("IFEN",     "Formatter enable", GP_IFEN),
    GPINFO_ENTRY("IOFL",     "Rewind/unload", GP_IOFL),
    GPINFO_ENTRY("ITAD1",    "Transport address 1 (LSB)", GP_ITAD1),
    GPINFO_ENTRY("IFAD",     "Formatter address", GP_IFAD),
    GPINFO_ENTRY("IDEN",     "*Speed select", GP_IDEN),
};

static const char daysofweek[] PROGMEM = {
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
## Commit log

2022-04-21 Unfinished version of 5V adapter for Arduino Mega 2560 R3 using KiCad 5.1.10. I'm planning on abondoning this because the Arduino Mega 2560 R3 simply isn't fast enough.
2022-05-05 Development checkpoint: started work on design for Adafruit Metro M4 Grand Central. I'm aborting that development path and switching to the Teensy 4.1 because it's far faster and actually available.
2022-05-19 Development checkpoint: schematic complete, passes ERC, started layout.
2022-05-19 Initial copy of spreadsheet with pins.
2022-05-20 Development checkpoint: added switchable controller/peripheral functionality.
2022-05-20 Added switchable controller/peripheral mode
2022-05-20 Development checkpoint: ready to start layout
2022-05-21 Development checkpoint: fully routed. Still 6 layers, but I'll chop that down right before tapeout.
2022-05-21 Development checkpoint: layout and routing completed; passes DRC
2022-05-22 Revision A for tapeout.
2022-05-22 Cleaned up a stray bit of silkscreen art off of the board. This is still revision A.
2022-05-22 Revision A, attempt #2
2022-05-22 Development checkpoint: revision A1 (added holes for feet)
2022-05-22 Ready to tape out Revision A1
2022-06-07 Development checkpoint: firmware builds and is able to 'testread' and rewind the tape.
2022-06-08 Development checkpoint: reads and writes tapes succesfully (I believe). Also now has 'date' command to allow seeing and changing the date.
2022-06-08 Rearranged slightly to optimize RAM use (by putting more stuff into Flash)
2022-06-10 Corrected names of OEA and DIRA/DIRB signals
2022-06-10 + increased tape data buffer from 4096 to 32768 bytes + added EOT detection for cmd_read() + expanded 'read' command to allow '-eot' and '-nfiles' + added 'erase' command + fixed 'testwrite' command 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
2022-06-11 + reworked GPIO interrupt setup mechanism + added 'peek' and 'poke' commands + moved all PCA9535 initialization code into separate function + added initialization of LPI2C4_INT (port expander interru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
2022-06-13 + added code to assert/deassert IFEN line for each command in an attempt to mitigate anomolous behavior when power is lost. Another goal is to allow the pertexus to be connected to multiple periphera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
2022-06-13 Fixed line endings
2022-11-30 Added README.md
2022-11-30 Added development notes from June 8-12
2022-11-30 Fixed some bugs in the 'help' command.
2022-11-30 Bugfix: 'sd read' command was not working correctly with n*2+1-length records (it needed to skip a byte at the end of such a record to keep header alignment)
2022-11-30 Updated README.md a little more.
2022-12-01 Bugfix: tmpfn_gen() would only look for TEMP0000.TMP. If that file already existed it would loop forever.
2022-12-01 Fixed generation of sorted symbol table to use 'objdump' instead of 'nm' so that section information is also presented.
2022-12-10 Added revision history and ECO notes
